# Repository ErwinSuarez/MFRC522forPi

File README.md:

SPI-Py: Hardware SPI as a C Extension for Python
======

COPYRIGHT (C) 2012 Louis Thiery. All rights reserved. Further work by Connor Wolf.

This program is free software; you can redistribute it and/or modify it under the terms of the GNU General Public License V2 as published by the Free Software Foundation.

LIABILITY  
This program is distributed for educational purposes only and is no way suitable for any particular application,
especially commercial. There is no implied suitability so use at your own risk!

This is still on development. Make sure to install Rasbian OS to raspberry pi to start working on this project

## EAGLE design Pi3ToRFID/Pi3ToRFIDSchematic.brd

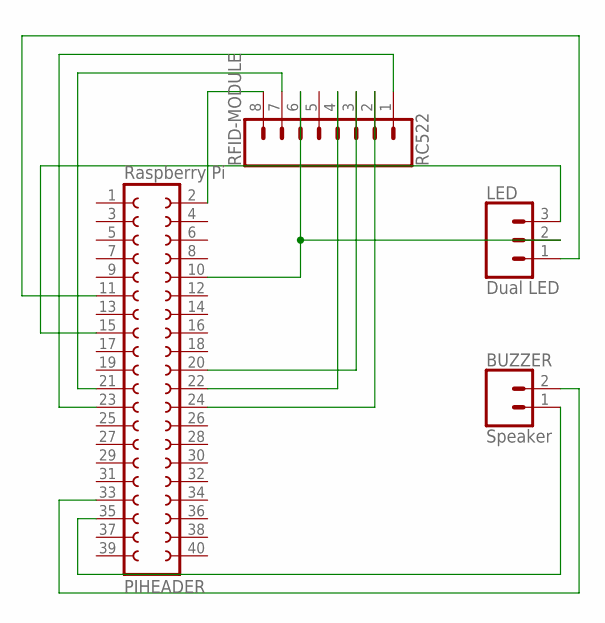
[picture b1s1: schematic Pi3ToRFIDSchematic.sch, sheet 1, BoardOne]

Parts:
BUZZER: Speaker; MOLEX-1X2
LED: Dual LED; MOLEX-1X3
PIHEADER: Raspberry Pi; FE20-2W
RFID-MODULE: RC522; 1X08_LONGPADS

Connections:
unnamed: PIHEADER.2, RFID-MODULE.8
unnamed: PIHEADER.21, RFID-MODULE.7
unnamed: PIHEADER.22, RFID-MODULE.4
unnamed: PIHEADER.20, RFID-MODULE.3
unnamed: PIHEADER.24, RFID-MODULE.2
unnamed: PIHEADER.23, RFID-MODULE.1
unnamed: BUZZER.2, PIHEADER.33
unnamed: LED.1, PIHEADER.11
unnamed: BUZZER.1, PIHEADER.35
unnamed: LED.3, PIHEADER.15
unnamed: LED.2, PIHEADER.10, RFID-MODULE.6

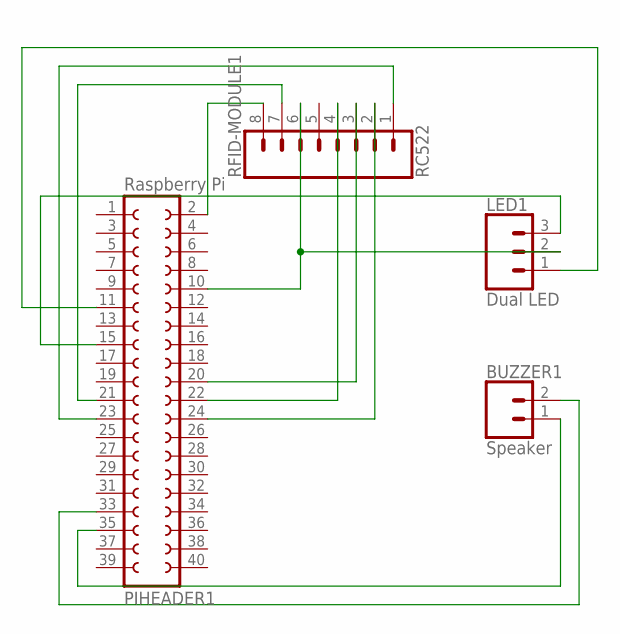
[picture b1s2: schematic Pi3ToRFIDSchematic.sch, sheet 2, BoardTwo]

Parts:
BUZZER1: Speaker; MOLEX-1X2
LED1: Dual LED; MOLEX-1X3
PIHEADER1: Raspberry Pi; FE20-2W
RFID-MODULE1: RC522; 1X08_LONGPADS

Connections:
unnamed: PIHEADER1.2, RFID-MODULE1.8
unnamed: PIHEADER1.21, RFID-MODULE1.7
unnamed: PIHEADER1.22, RFID-MODULE1.4
unnamed: PIHEADER1.20, RFID-MODULE1.3
unnamed: PIHEADER1.24, RFID-MODULE1.2
unnamed: PIHEADER1.23, RFID-MODULE1.1
unnamed: BUZZER1.2, PIHEADER1.33
unnamed: BUZZER1.1, PIHEADER1.35
unnamed: LED1.3, PIHEADER1.15
unnamed: LED1.1, PIHEADER1.11
unnamed: LED1.2, PIHEADER1.10, RFID-MODULE1.6

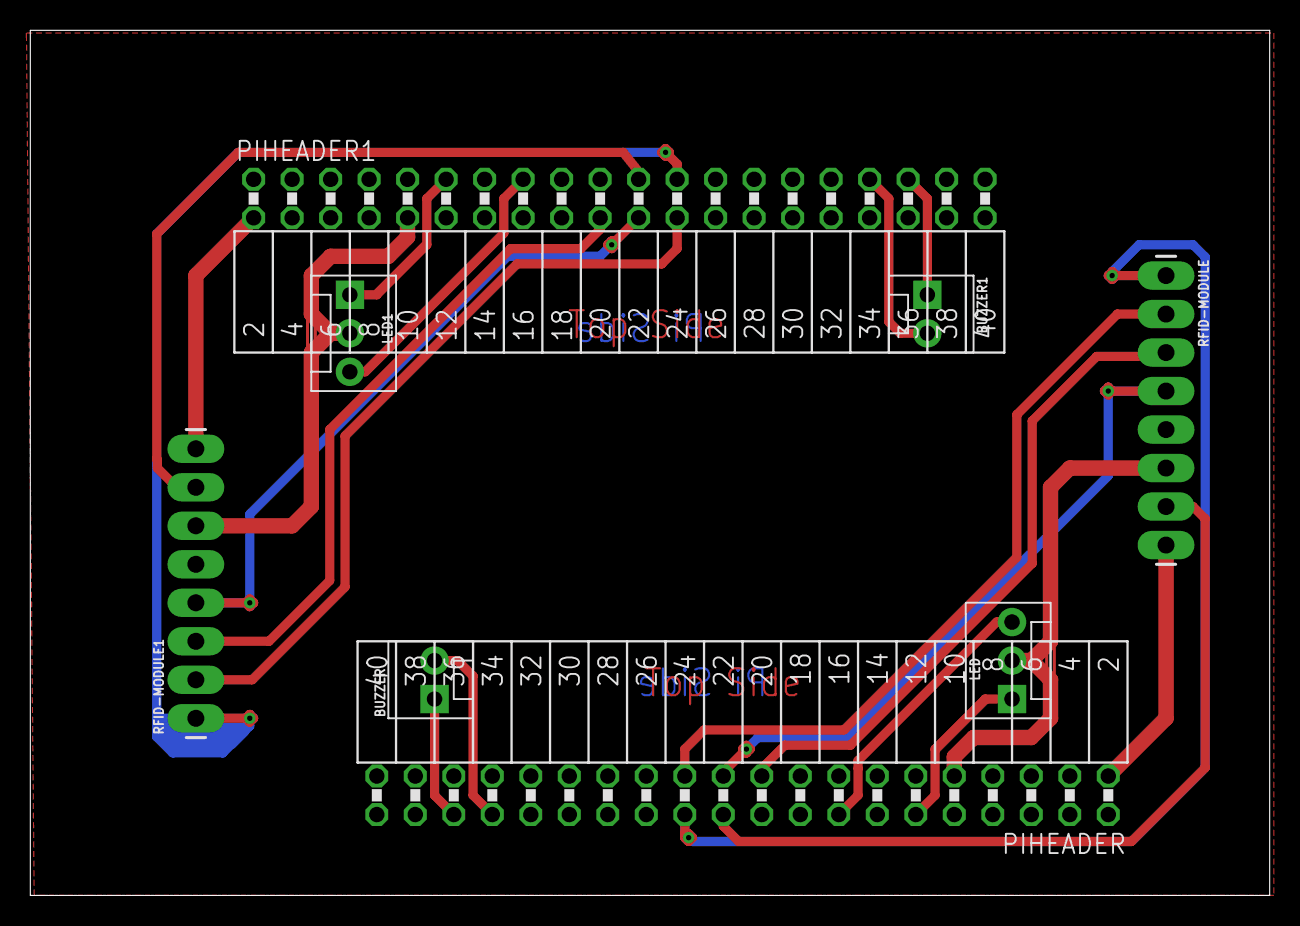
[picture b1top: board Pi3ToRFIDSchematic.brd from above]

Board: 2 copper layers, 81.8 x 57.1 mm, 8 parts (0 on the bottom side), 22 nets.

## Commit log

2018-05-16 Create eventDBv2.sql
    Database Schema
2018-05-16 Add files via upload
    Added files needed for SPI
2018-05-16 Add files via upload
    Added files for MFRC and sample Read Script
2018-05-16 Create Read_new.py
    Read UID and record into database
2018-05-28 Insert deps record
    Insert a sample deps record to eventDBv2
2018-05-28 Insert a sample rooms record
    Insert a sample record to rooms
2018-05-31 Update recordToDb.sql
    changed sequence of calling roomID to description
2018-05-31 Update Read_new.py
    changed print format and missing string
2018-05-31 Update Read_new.py
    updated indent of code.
2018-05-31 Update MFRC522.py
    updated indet
2018-05-31 Update README.md
    need to install Rasbian OS
2018-05-31 Update eventDBv2.sql
    updated the attributes of table
2018-05-31 Create sampleEmpsRecords.sql
    sample employees record
2018-05-31 Update Read_new.py
    changed authorization
2018-05-31 Update MFRC522.py
    add missing parameter in switchPin function
2018-05-31 Update MFRC522.py
    changed setup pins for Pi and set by default to low
2018-05-31 Update eventDBv2.sql
    updated availability table
2018-05-31 Update Read_new.py
    changed switchPin and formatto call procedure
2018-05-31 Update MFRC522.py
    changed switchpin logic to 1
2018-05-31 Update Read_new.py
    modified getAuthentication method to position 0
2018-05-31 Update Read_new.py
    Error presented during runtime. modified recordToDb format to call procdure
2018-05-31 Rename sampleRoomsRecord.sql to sampleRoomsRecords.sql
    change file name
2018-05-31 Create masterDBv2.sql
    Created masterDB for master Pi
2018-06-01 Create README.txt
    Initial commit
2018-06-01 Rename README.txt to Pi3ToRFID/README.txt
2018-06-01 Update masterDBv2.sql
    changed database name
2018-06-01 Update masterDBv2.sql
    used masterDBv2

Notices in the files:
parts and their libraries:
SparkFun-Connectors: Licensing: Creative Commons ShareAlike 4.0 International - https://creativecommons.org/licenses/by-sa/4.0
